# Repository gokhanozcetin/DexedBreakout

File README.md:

DexedBreakout is a small Raspberry Pi Hat that fits into of the shelf RPI cases with small modifications. The connections are aligned to RPI connectors so that the assmebly can be enclosed easily.

It includes a PCM5102 DAC, a 0.96 inch OLED and a rotary encoder. The PCB is arranged so that the OLED centers the Raspberry. It offers TRS type MIDI IN, a true hardware TRS type MIDI THRU and a stereo audio output jack.

The MIDI IN is connected to RX pin of the Raspberry PI I/O. MIDI THRU port replicates the MIDI IN signal via a buffer chip.

PCM5102 is configured to run in I2S mode and configuration pins are hardwired.

The Encoder is KY-040 type encoder. A/CLK is connected to GPIO9, B/DAT is connected to GPIO10 and switch is connected to GPIO11.

The 40 pin I/O header is designed to be a female regular input. A passthrough type would be much nicer to lower the position of the card however neither SMT nor THT pass-through connectors fit since the I/O is very close to the edge. It is possible not to populate the female header and directly solder the card to the RPI to lower the height and fit the assembly in to a case.

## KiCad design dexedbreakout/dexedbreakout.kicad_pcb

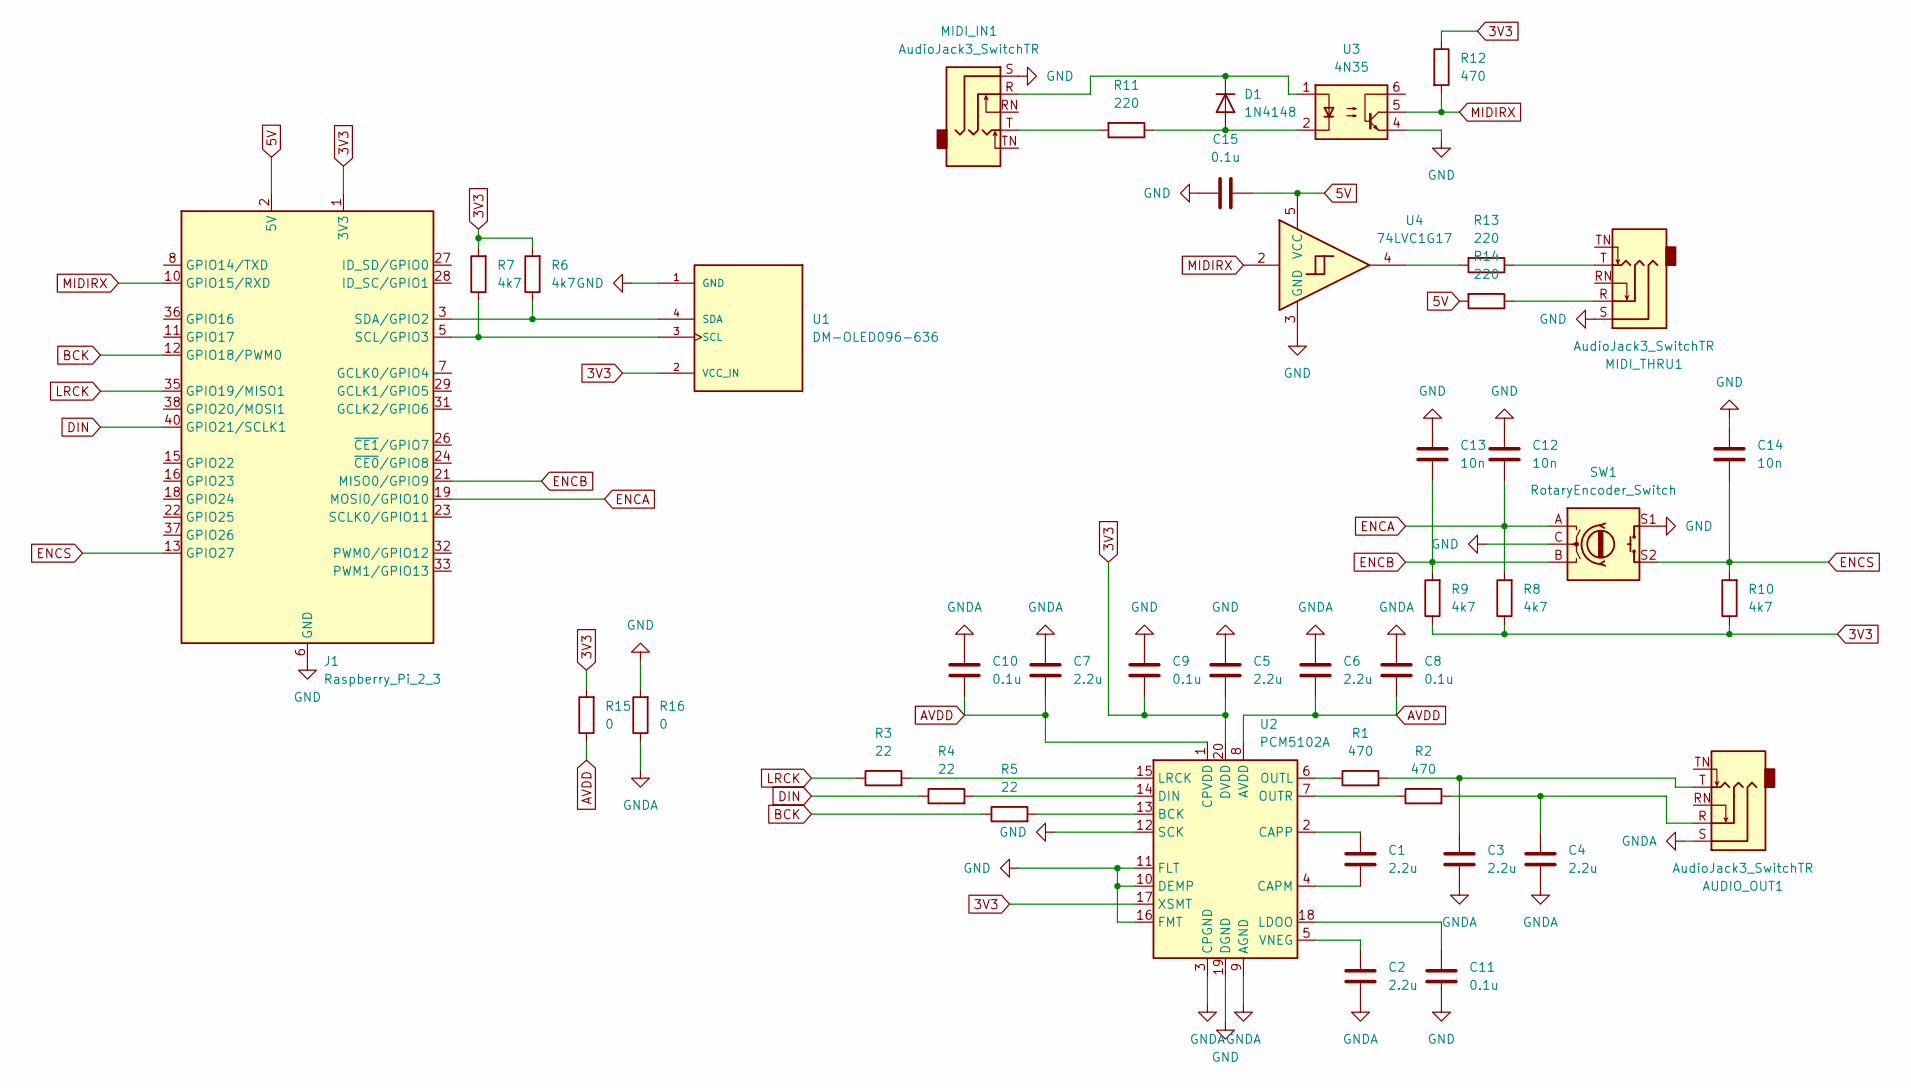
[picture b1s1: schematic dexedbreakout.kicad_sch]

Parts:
AUDIO_OUT1: AudioJack3_SwitchTR; Jack_3.5mm_CUI_SJ1-3525N_Horizontal
C1, C2, C3, C4, C5, C6, C7: 2.2u; C_0603_1608Metric
C8, C9, C10, C11, C15: 0.1u; C_0603_1608Metric
C12, C13, C14: 10n; C_0603_1608Metric
D1: 1N4148; D_DO-35_SOD27_P7.62mm_Horizontal
J1: Raspberry_Pi_2_3; PinSocket_2x20_P2.54mm_Vertical
MIDI_IN1: AudioJack3_SwitchTR; Jack_3.5mm_CUI_SJ1-3525N_Horizontal
MIDI_THRU1: AudioJack3_SwitchTR; Jack_3.5mm_CUI_SJ1-3525N_Horizontal
R1, R2, R12: 470; R_0603_1608Metric
R3, R4, R5: 22; R_0603_1608Metric
R6, R7, R8, R9, R10: 4k7; R_0603_1608Metric
R11, R13, R14: 220; R_0603_1608Metric
R15, R16: 0; R_0603_1608Metric
SW1: RotaryEncoder_Switch; RotaryEncoder_Alps_EC11E-Switch_Vertical_H20mm_CircularMoun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
U1: DM-OLED096-636; MODULE_DM-OLED096-636; PARTREV 2018-09-10
U2: PCM5102A; TSSOP-20_4.4x6.5mm_P0.65mm
U3: 4N35; DIP-6_W7.62mm
U4: 74LVC1G17; SOT-23-5_HandSoldering

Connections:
3V3: C5.2, C9.2, J1.1 (3V3), J1.17 (3V3), R6.2, R7.2, R8.1, R9.1, R10.1, R12.1, R15.2, U1.2 (VCC_IN), U2.17 (XSMT), U2.20 (DVDD)
5V: C15.2, J1.2 (5V), J1.4 (5V), R14.2, U4.5 (VCC)
AVDD: C6.2, C7.2, C8.2, C10.2, R15.1, U2.1 (CPVDD), U2.8 (AVDD)
BCK: J1.12 (GPIO18/PWM0), R5.1
DIN: J1.40 (GPIO21/SCLK1), R4.1
ENCA: C12.2, J1.19 (MOSI0/GPIO10), R8.2, SW1.A
ENCB: C13.2, J1.21 (MISO0/GPIO9), R9.2, SW1.B
ENCS: C14.2, J1.13 (GPIO27), R10.2, SW1.S2
GND: C5.1, C9.1, C11.2, C12.1, C13.1, C14.1, C15.1, J1.6 (GND), J1.9 (GND), J1.14 (GND), J1.20 (GND), J1.25 (GND), J1.30 (GND), J1.34 (GND), J1.39 (GND), MIDI_IN1.S, MIDI_THRU1.S, R16.2, SW1.C, SW1.S1, U1.1 (GND), U2.10 (DEMP), U2.11 (FLT), U2.12 (SCK), U2.16 (FMT), U2.19 (DGND), U3.4, U4.3 (GND)
GNDA: AUDIO_OUT1.S, C2.2, C3.2, C4.2, C6.1, C7.1, C8.1, C10.1, R16.1, U2.3 (CPGND), U2.9 (AGND)
LRCK: J1.35 (GPIO19/MISO1), R3.1
MIDIRX: J1.10 (GPIO15/RXD), R12.2, U3.5, U4.2
unnamed: AUDIO_OUT1.R, C4.1, R2.2
unnamed: AUDIO_OUT1.T, C3.1, R1.2
unnamed: D1.2 (A), R11.1, U3.2
unnamed: D1.1 (K), MIDI_IN1.R, U3.1
unnamed: J1.5 (SCL/GPIO3), R7.1, U1.3 (SCL)
unnamed: J1.3 (SDA/GPIO2), R6.1, U1.4 (SDA)
unnamed: MIDI_IN1.T, R11.2
unnamed: MIDI_THRU1.R, R14.1
unnamed: MIDI_THRU1.T, R13.1
unnamed: R13.2, U4.4
unnamed: R5.2, U2.13 (BCK)
unnamed: C1.2, U2.4 (CAPM)
unnamed: C1.1, U2.2 (CAPP)
unnamed: R4.2, U2.14 (DIN)
unnamed: C11.1, U2.18 (LDOO)
unnamed: R3.2, U2.15 (LRCK)
unnamed: R1.1, U2.6 (OUTL)
unnamed: R2.1, U2.7 (OUTR)
unnamed: C2.1, U2.5 (VNEG)

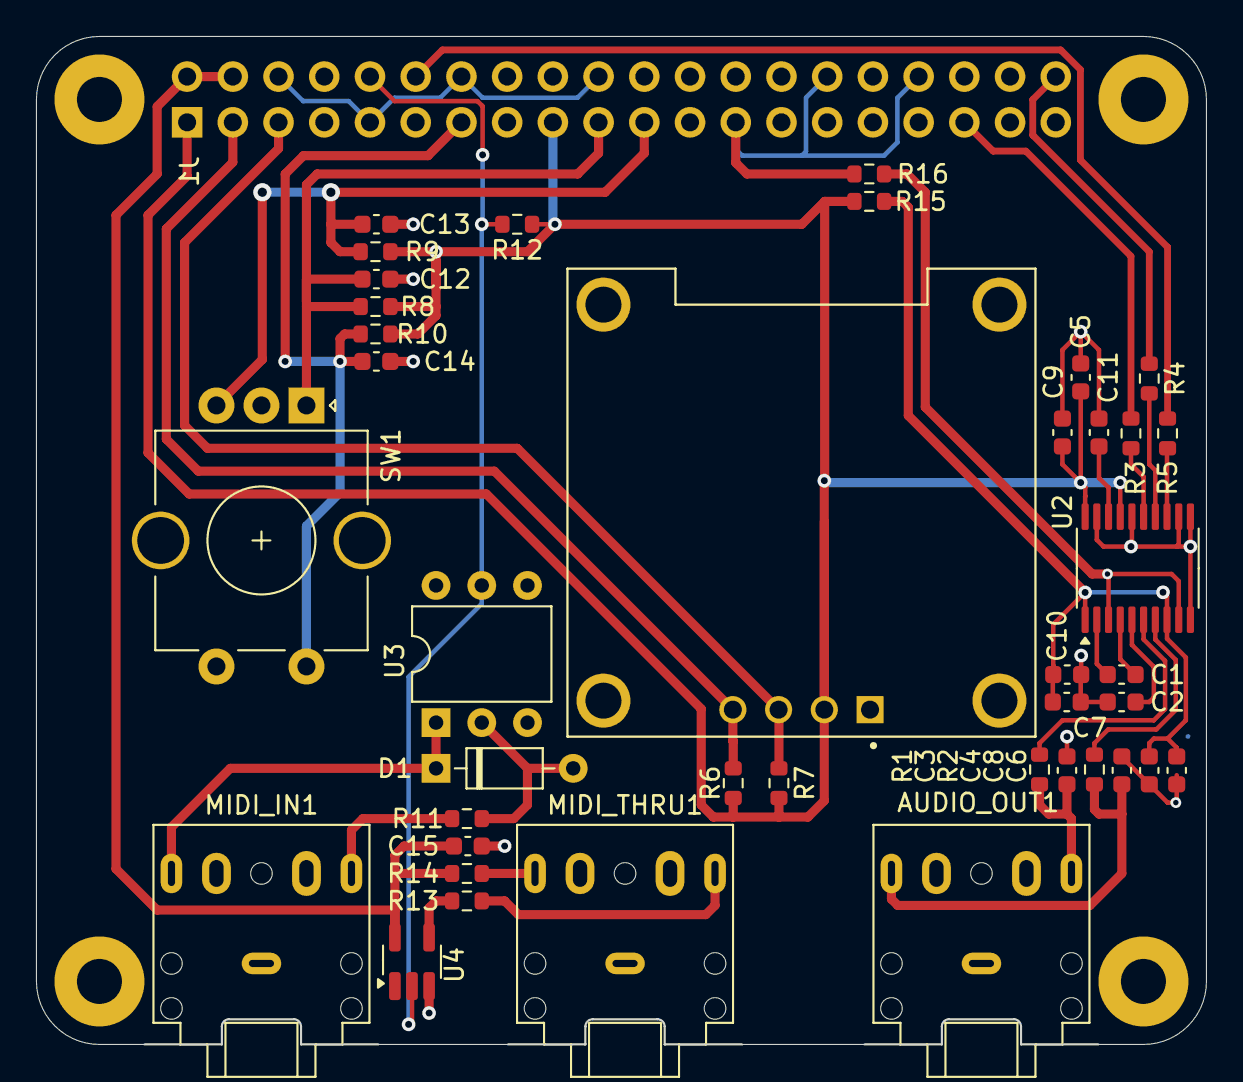
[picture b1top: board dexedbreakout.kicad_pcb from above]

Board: 2 copper layers, 64.9 x 56.0 mm, 41 parts (1 on the bottom side), 31 nets.
